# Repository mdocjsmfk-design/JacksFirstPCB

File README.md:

# JacksFirstPCB
JacksFirstPCB
This is a simon says game I made using a PCB. It has buttons and LEDs and you repeat the pattern like the normal game.

why I made it
I made this because I needed a pretty easy first PCB project to get done. I also used to play simon says a lot when I was younger so I thought it would be cool to remake it myself.

what it does
It’s just a small game you can play when you’re bored or want something to mess with. It also helped me understand how PCBs work a little better.

[Pathfinder BOM - Sheet1.pdf](https://github.com/user-attachments/files/27326980/Pathfinder.BOM.-.Sheet1.pdf)

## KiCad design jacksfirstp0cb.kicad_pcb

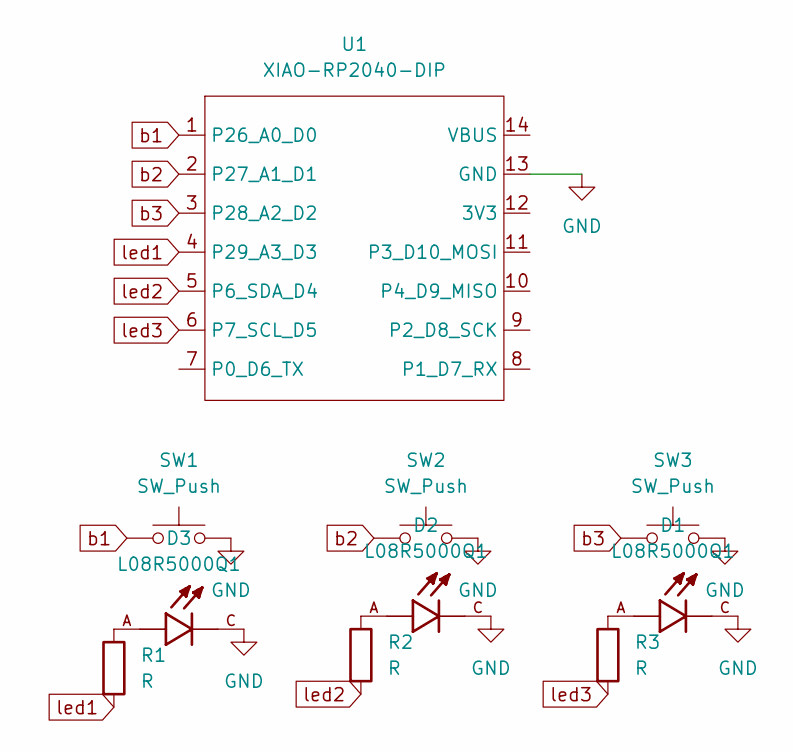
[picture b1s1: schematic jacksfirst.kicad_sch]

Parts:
D1, D2, D3: L08R5000Q1; LEDRD254W57D500H1070; PARTREV NA
R1, R2, R3: R; R_Axial_DIN0204_L3.6mm_D1.6mm_P5.08mm_Horizontal
SW1, SW2, SW3: SW_Push; SW_Cherry_MX_1.00u_PCB
U1: XIAO-RP2040-DIP

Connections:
GND: D1.C, D2.C, D3.C, SW1.2, SW2.2, SW3.2, U1.13 (GND)
unnamed: D1.A, R3.1
unnamed: D2.A, R2.1
unnamed: D3.A, R1.1
b1: SW1.1, U1.1 (P26_A0_D0)
b2: SW2.1, U1.2 (P27_A1_D1)
b3: SW3.1, U1.3 (P28_A2_D2)
led1: R1.2, U1.4 (P29_A3_D3)
led2: R2.2, U1.5 (P6_SDA_D4)
led3: R3.2, U1.6 (P7_SCL_D5)

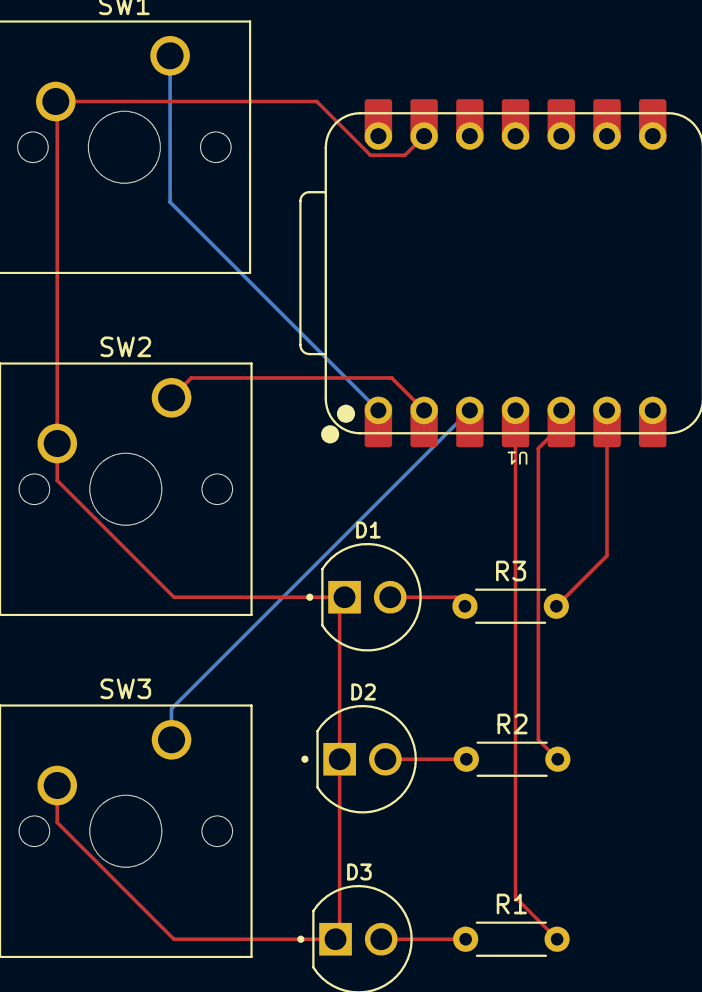
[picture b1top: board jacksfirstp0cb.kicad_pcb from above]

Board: 2 copper layers, 10 parts (0 on the bottom side), 10 nets.

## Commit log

2026-04-04 Add Simon Says game implementation
2026-04-06 Add image to README for Simon says game
2026-04-28 Enhance README with project details and new image
    Updated the README to include a new image and improved project description.
2026-04-28 Add BOM for PCB prototype components
2026-04-28 Add PCB prototype details to README
2026-05-04 Add link to Untitled spreadsheet PDF in README
2026-05-04 Update README with new BOM link and remove old PDF
    Removed outdated PDF link and added BOM link.
2026-05-04 Add link to Pathfinder project in BOM
    Updated BOM with a link to the Pathfinder project PDF.
